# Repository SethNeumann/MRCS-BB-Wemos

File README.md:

# REPO NAME: MRCS-BB-Wemos

## License: Creative Commons Attribution-NonCommercial-ShareAlike

This board contains a Wemos D1 processor, 1A regulator, level shifters and an MCP23017 to provide a rougth equivalent to a BB-Leo.

The Wemos D1 has considerably more code space than a ProMini/Leonardo
and could eventually support a "local fall back" mode when no CMRINet
is present and may support other protocols over WiFi.  It will use
John Plochers forthcoming cpNode sketch.

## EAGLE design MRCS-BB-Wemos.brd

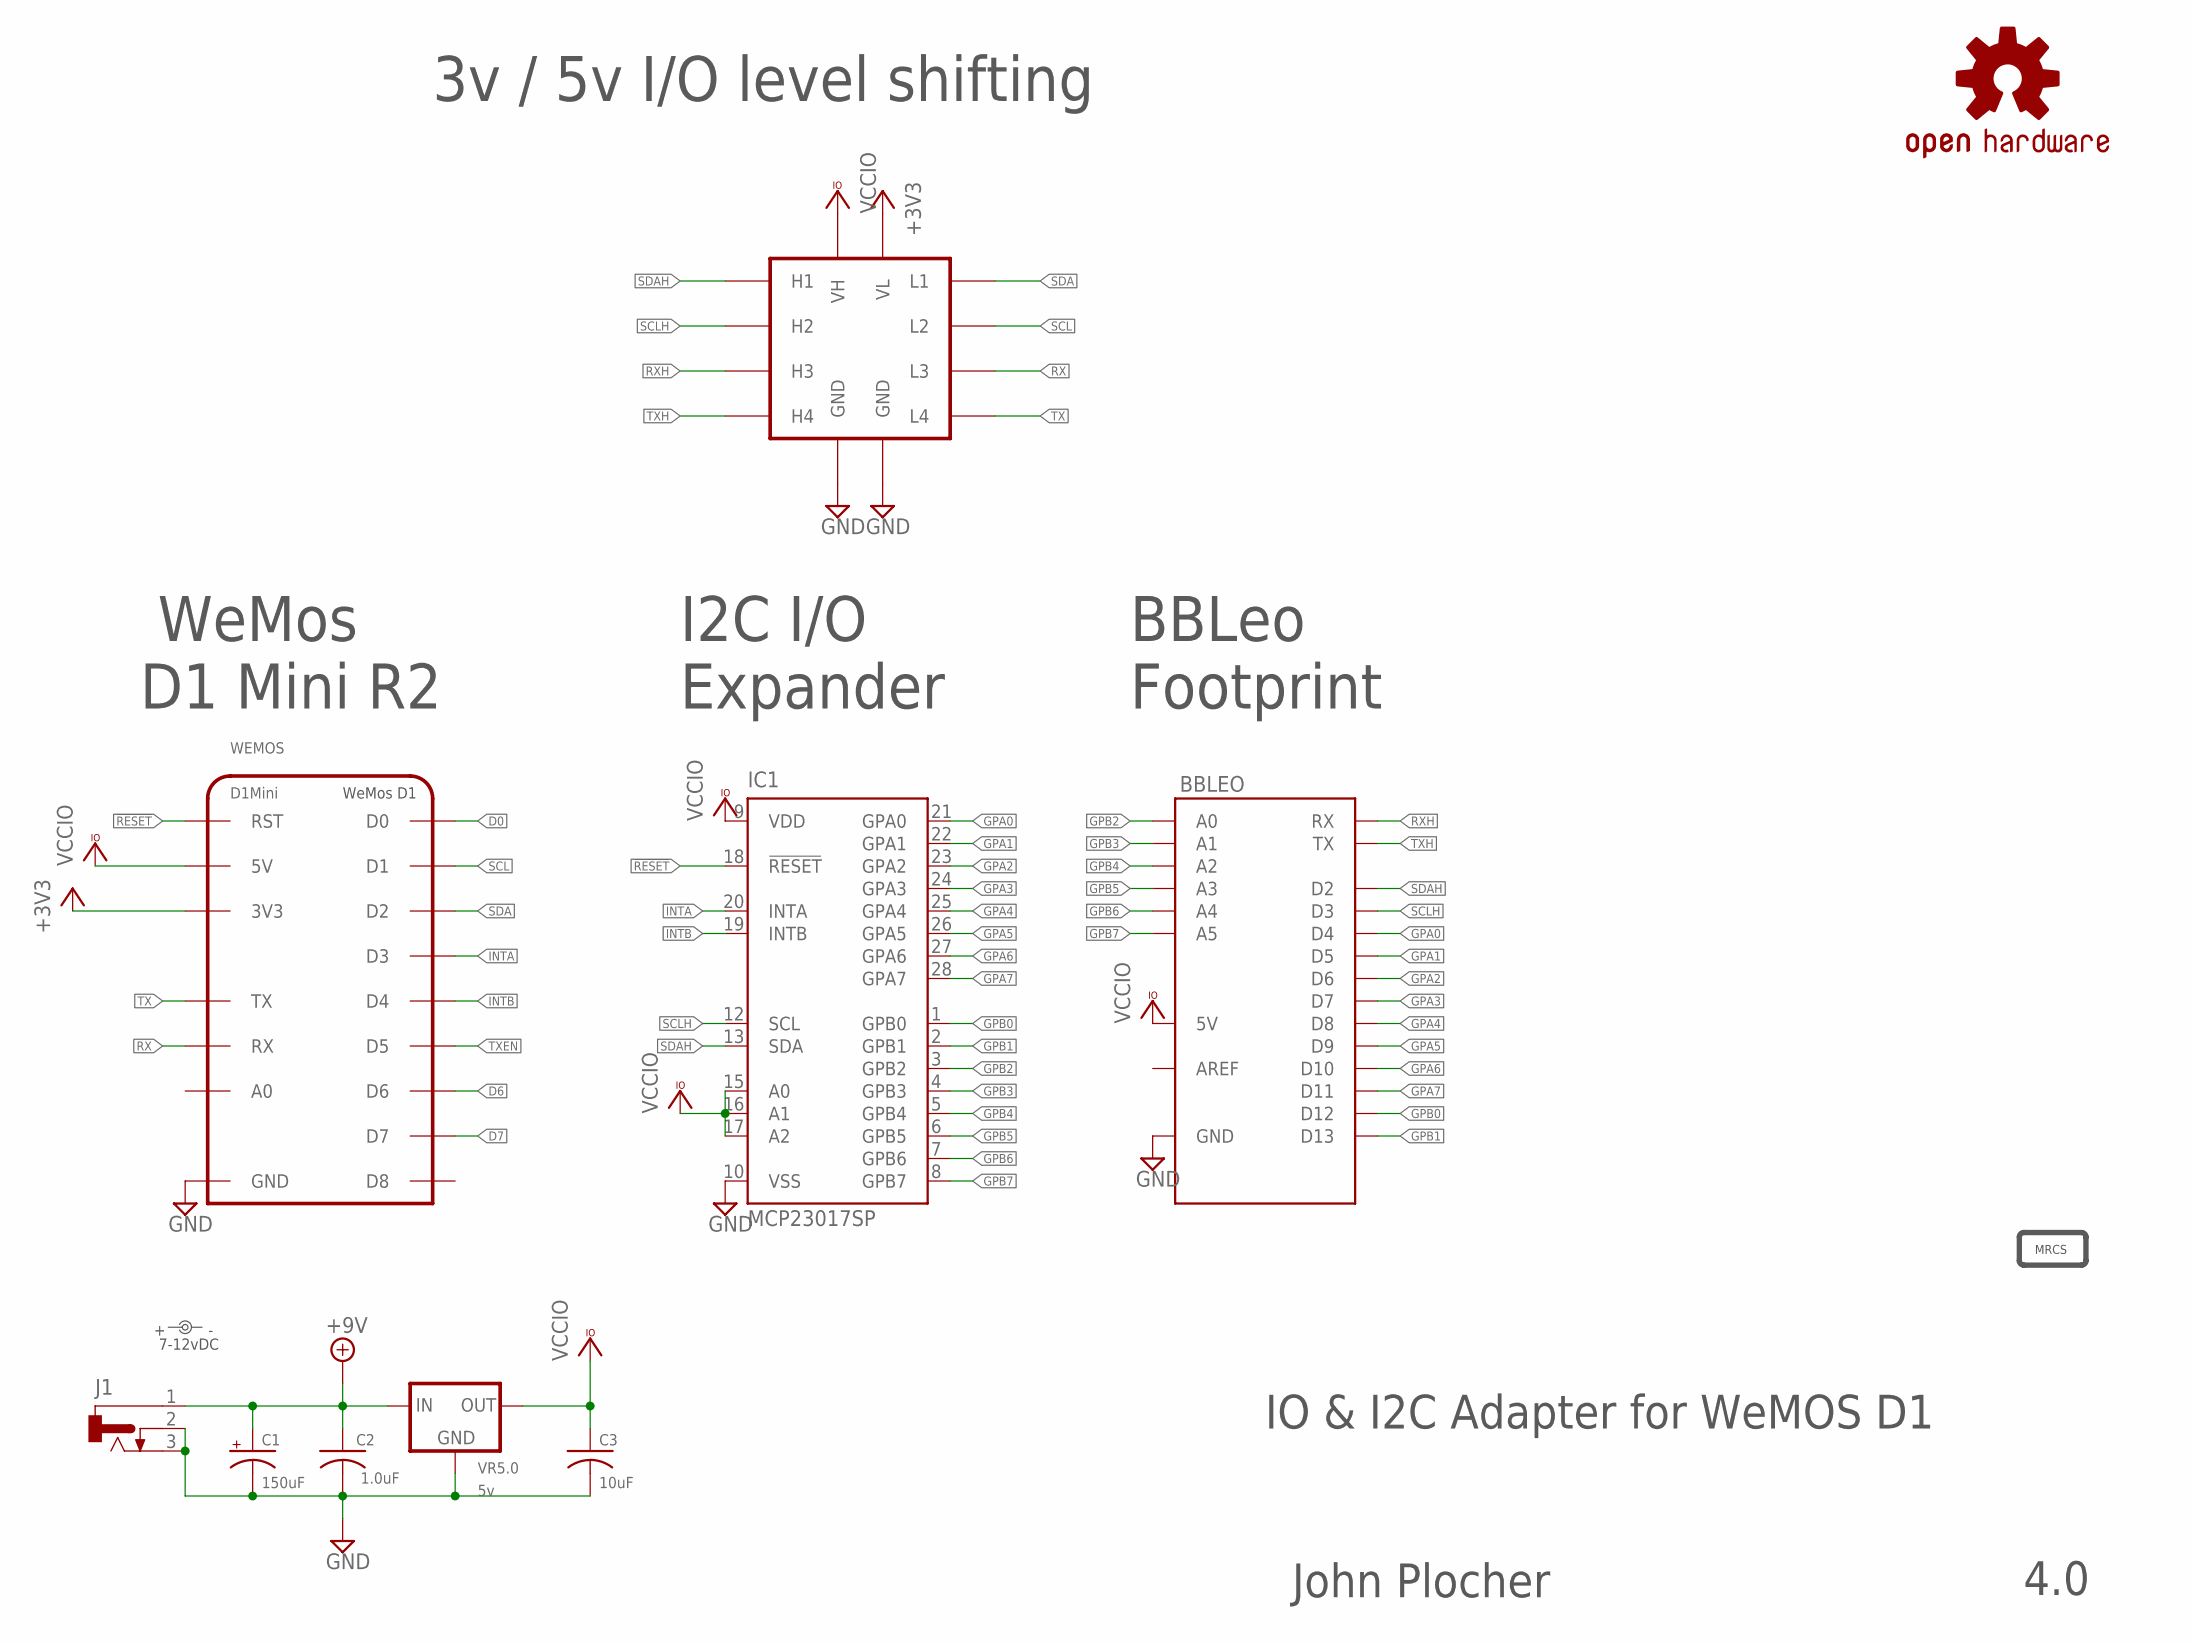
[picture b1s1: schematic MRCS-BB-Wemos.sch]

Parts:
BBLEO: ARDUINO-BBLEO
C1: 150uF; E5-10.5
C2: 1.0uF; C050-024X044
C3: 10uF; C050-024X044
IC1: MCP23017SP; DIL28-3
J1: CONNECTOR-DC-POWER-RA; DCJ0202
LABEL1: 7-12vDC; PWR_LABEL
LS2: I2C-LEVELSHIFTER; MODULE
OSHW1: DOC-OSHW-LOGO-L; OSHW-LOGO-L
U$1: DOC-MRCS-LOGOTOP; MRCS-LOGO
VR5.0: 5v; TO-220-RA
WEMOS: D1Mini; WEMOS-D1

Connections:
!RESET: IC1.18 (!RESET), WEMOS.RST
+3V3: LS2.LV (VL), WEMOS.3V3
+9V: C1.+, C2.1, J1.1, VR5.0.IN
D0: WEMOS.D0
D6: WEMOS.D6
D7: WEMOS.D7
GND: BBLEO.GND@0 (GND), BBLEO.GND@1 (GND), BBLEO.GND@2 (GND), BBLEO.GND@3 (GND), BBLEO.GND@4 (GND), C1.-, C2.2, C3.2, IC1.10 (VSS), J1.2, J1.3, LS2.GND@0 (GND), LS2.GND@1 (GND), VR5.0.GND, WEMOS.GND
GPA0: BBLEO.D4, IC1.21 (GPA0)
GPA1: BBLEO.D5, IC1.22 (GPA1)
GPA2: BBLEO.D6, IC1.23 (GPA2)
GPA3: BBLEO.D7, IC1.24 (GPA3)
GPA4: BBLEO.D8, IC1.25 (GPA4)
GPA5: BBLEO.D9, IC1.26 (GPA5)
GPA6: BBLEO.D10, IC1.27 (GPA6)
GPA7: BBLEO.D11, IC1.28 (GPA7)
GPB0: BBLEO.D12, IC1.1 (GPB0)
GPB1: BBLEO.D13, IC1.2 (GPB1)
GPB2: BBLEO.A0, IC1.3 (GPB2)
GPB3: BBLEO.A1, IC1.4 (GPB3)
GPB4: BBLEO.A2, IC1.5 (GPB4)
GPB5: BBLEO.A3, IC1.6 (GPB5)
GPB6: BBLEO.A4, IC1.7 (GPB6)
GPB7: BBLEO.A5, IC1.8 (GPB7)
INTA: IC1.20 (INTA), WEMOS.D3
INTB: IC1.19 (INTB), WEMOS.D4
RX: LS2.L3, WEMOS.RX
RXH: BBLEO.RX, LS2.H3
SCL: LS2.L2, WEMOS.D1
SCLH: BBLEO.SCL (D3), IC1.12 (SCL), LS2.H2
SDA: LS2.L1, WEMOS.D2
SDAH: BBLEO.SDA (D2), IC1.13 (SDA), LS2.H1
TX: LS2.L4, WEMOS.TX
TXEN: WEMOS.D5
TXH: BBLEO.TX, LS2.H4
VCCIO: BBLEO.+5V@1 (5V), BBLEO.+5V@2 (5V), BBLEO.+5V@3 (5V), BBLEO.+5V@4 (5V), C3.1, IC1.9 (VDD), IC1.15 (A0), IC1.16 (A1), IC1.17 (A2), LS2.HV (VH), VR5.0.OUT, WEMOS.5V

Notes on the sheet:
IO & I2C Adapter for WeMOS D1
John Plocher
4.0
WeMos D1 Mini R2
3v / 5v I/O level shifting
I2C I/O Expander
BBLeo Footprint

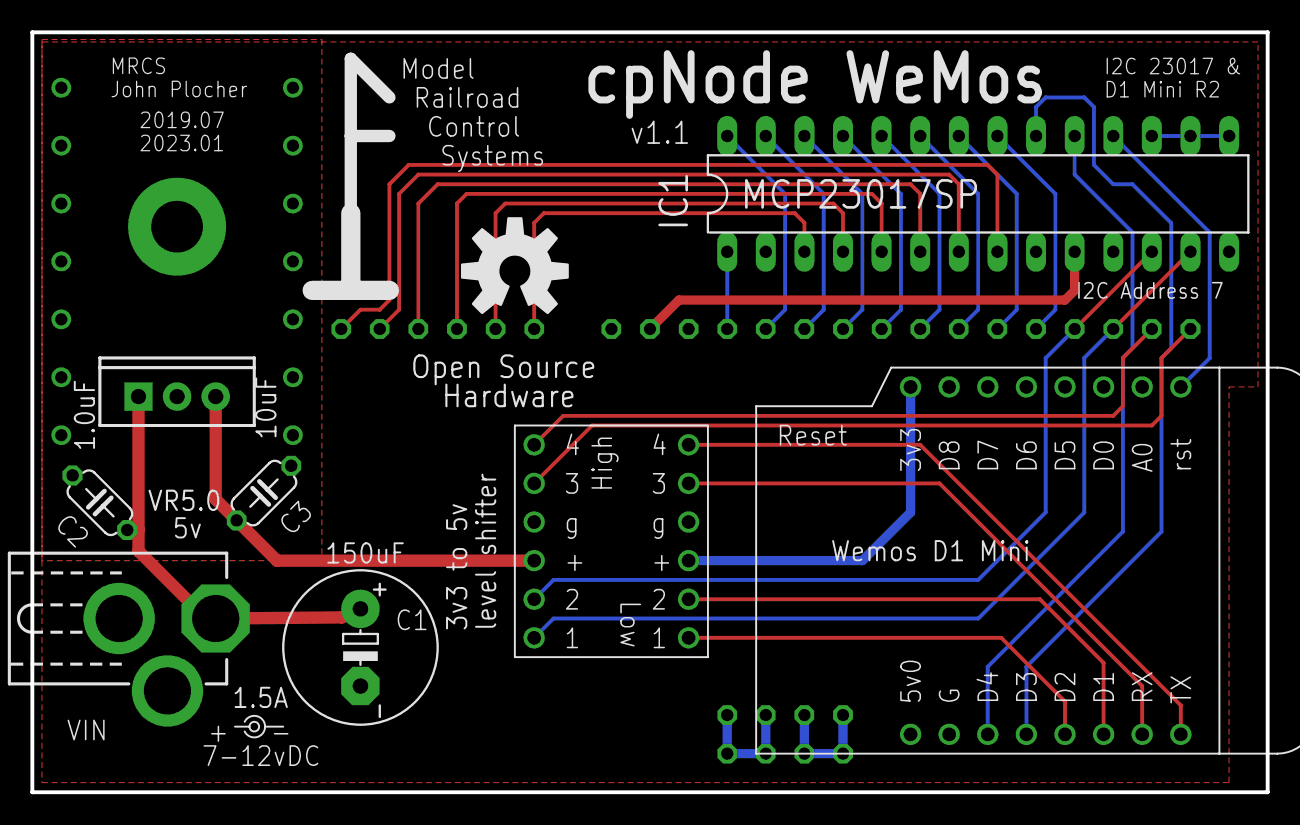
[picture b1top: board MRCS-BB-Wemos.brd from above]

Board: 2 copper layers, 81.3 x 50.0 mm, 12 parts (0 on the bottom side), 31 nets.

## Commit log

2021-02-23 intial commit
2021-02-23 Update INFO
2021-02-23 moved BB-Wemos from EAGLE directory
    we made a short run of these, which Dennis Drumheller bought.
2023-01-14 replace / update components with newer ones in SPCoast library clean up silk screen, add MRCS
2023-01-14 updated INFO
2023-01-14 replace VR with RA version & mounting hole to W/A an eagle bug Add MRCS to sch

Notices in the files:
parts and their libraries:
SPCoast: http://freedomdefined.org/OSHW Creative Commons - Attribution - ShareAlike 3.0
